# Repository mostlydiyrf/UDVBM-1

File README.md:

# UDVBM-1
Kicad (ver.6) design files, Arduino sketches, and user documents.

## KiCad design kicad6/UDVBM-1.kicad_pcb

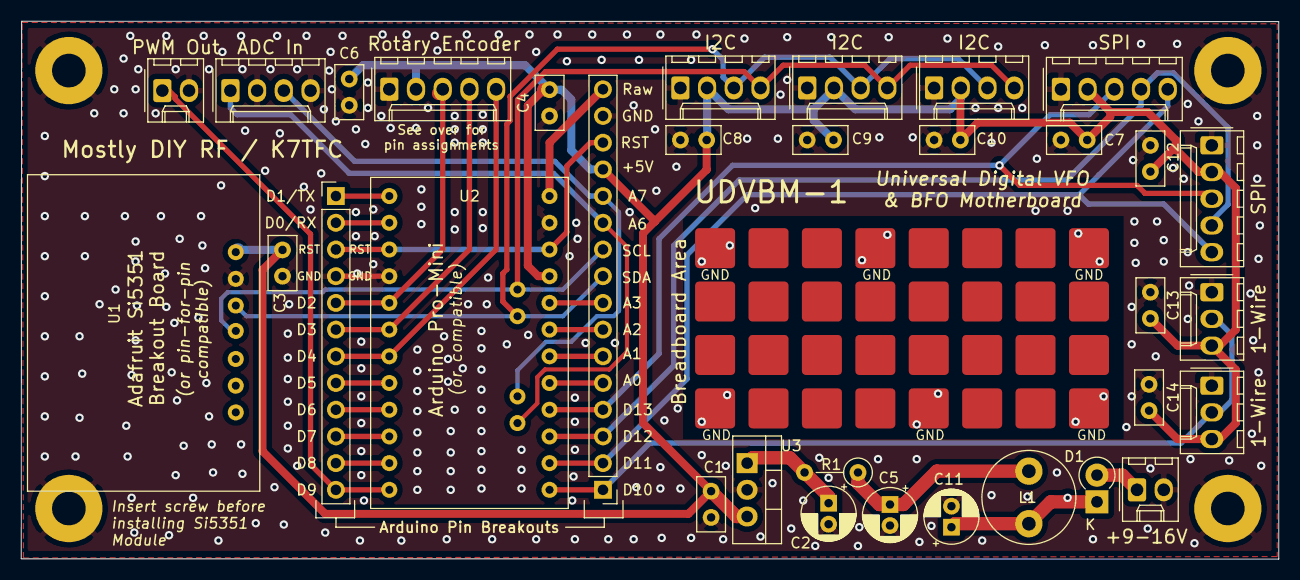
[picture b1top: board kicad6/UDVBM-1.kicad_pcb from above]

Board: 2 copper layers, 119.6 x 51.1 mm, 37 parts (0 on the bottom side), 30 nets.

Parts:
1-Wire: One-Wire Port 1; Molex_KK-254_AE-6410-03A_1x03_P2.54mm_Vertical
1-Wire#2: One-Wire Port 2; Molex_KK-254_AE-6410-03A_1x03_P2.54mm_Vertical
ADC In: ADC Inputs; Molex_KK-254_AE-6410-04A_1x04_P2.54mm_Vertical
C1, C3, C4, C6, C7, C8, C9, C10, C12, C13, C14: 0.10; C_Disc_D5.0mm_W2.5mm_P2.50mm
C2: 10uF; CP_Radial_D5.0mm_P2.00mm
C5, C11: 220uF; CP_Radial_D5.0mm_P2.00mm
D1: 1N4001; D_DO-41_SOD81_P2.54mm_Vertical_KathodeUp
H1, H2, H3, H4: Mounting_Hole_4-40; MountingHole_3.2mm_M3_Pad
I2C: I2C Port 1; Molex_KK-254_AE-6410-04A_1x04_P2.54mm_Vertical
I2C#2: I2C Port 3; Molex_KK-254_AE-6410-04A_1x04_P2.54mm_Vertical
I2C#3: I2C Port 2; Molex_KK-254_AE-6410-04A_1x04_P2.54mm_Vertical
J1: 12VDC; Molex_KK-254_AE-6410-02A_1x02_P2.54mm_Vertical
J2: Arduino Left Breakout; PinHeader_1x12_P2.54mm_Vertical
J3: Arduino Right Breakout; PinHeader_1x16_P2.54mm_Vertical
L1: 1.0mH; L_Radial_D8.7mm_P5.00mm_Fastron_07HCP
PWM Out: PWM Out; Molex_KK-254_AE-6410-02A_1x02_P2.54mm_Vertical
R1: 10; R_Axial_DIN0207_L6.3mm_D2.5mm_P5.08mm_Vertical
Rotary Encoder: Rotary Encoder; Molex_KK-254_AE-6410-05A_1x05_P2.54mm_Vertical
SPI: SPI Port 1; Molex_KK-254_AE-6410-05A_1x05_P2.54mm_Vertical
SPI#2: SPI Port 2; Molex_KK-254_AE-6410-05A_1x05_P2.54mm_Vertical
U1: Si5351A_Adafruit
U2: ArduinoPro_Mini; Arduino_Pro_Mini
U3: LM7805; TO-220-3_Vertical

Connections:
+5V: 1-Wire.3, 1-Wire#2.3, C1.1, C3.2, C4.2, C6.2, C7.2, C8.2, C9.2, C10.2, C12.2, C13.2, C14.2, I2C.2, I2C#2.2, I2C#3.2, J3.13, Rotary Encoder.2, SPI.2, SPI#2.2, U1.6, U2.22, U3.3
/1wire: 1-Wire.2, 1-Wire#2.2, J3.1, U2.10
/ADC1: ADC In.1, J3.11, U2.20
/ADC2: ADC In.3, J3.12, U2.21
/D0: J2.2, U2.0
/D1: J2.1, U2.1
/D2: J2.5, Rotary Encoder.3, U2.2
/D3: J2.6, Rotary Encoder.4, U2.3
/D4: J2.7, Rotary Encoder.5, U2.4
/D5: J2.8, U2.5
/D6: J2.9, U2.6
/D7: J2.10, U2.7
/D8: J2.11, U2.8
/D9: J2.12, PWM Out.1, U2.9
/D14: J3.5, U2.14
/D15: J3.6, U2.15
/D16: J3.7, U2.16
/D17: J3.8, U2.17
/MISO: J3.3, SPI.4, SPI#2.4, U2.12
/MOSI: J3.2, SPI.5, SPI#2.5, U2.11
/RST: J2.3, J3.14, U2.23, U2.27
/Raw: J3.16, U2.25
/SCK: J3.4, SPI.3, SPI#2.3, U2.13
/SCL: I2C.4, I2C#2.4, I2C#3.4, J3.10, U1.3, U2.19
/SDA: I2C.3, I2C#2.3, I2C#3.3, J3.9, U1.4, U2.18
GND: 1-Wire.1, 1-Wire#2.1, ADC In.2, ADC In.4, C1.2, C2.2, C3.1, C4.1, C5.2, C6.1, C7.1, C8.1, C9.1, C10.1, C11.2, C12.1, C13.1, C14.1, I2C.1, I2C#2.1, I2C#3.1, J1.2, J2.4, J3.15, PWM Out.2, Rotary Encoder.1, SPI.1, SPI#2.1, U1.5, U2.24, U2.26, U3.2
unnamed: C2.1, R1.2, U3.1
unnamed: C5.1, L1.1, R1.1
unnamed: C11.1, D1.1, L1.2
unnamed: D1.2, J1.1

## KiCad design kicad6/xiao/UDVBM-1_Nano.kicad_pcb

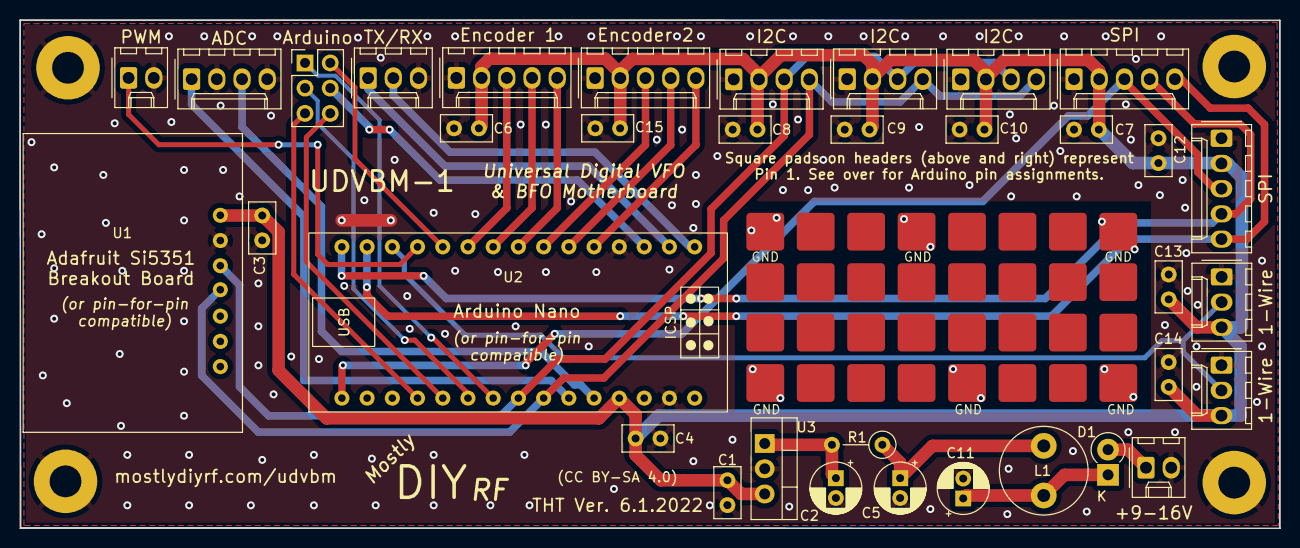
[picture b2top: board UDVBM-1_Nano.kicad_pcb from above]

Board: 2 copper layers, 126.9 x 51.2 mm, 39 parts (0 on the bottom side), 29 nets.

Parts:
1-Wire: One-Wire Port 1; Molex_KK-254_AE-6410-03A_1x03_P2.54mm_Vertical
1-Wire#2: One-Wire Port 2; Molex_KK-254_AE-6410-03A_1x03_P2.54mm_Vertical
ADC: ADC Inputs; Molex_KK-254_AE-6410-04A_1x04_P2.54mm_Vertical
Arduino: Arduino Pins; PinHeader_2x03_P2.54mm_Vertical
C1, C3, C4, C6, C7, C8, C9, C10, C12, C13, C14, C15: 0.10; C_Disc_D5.0mm_W2.5mm_P2.50mm
C2: 10uF; CP_Radial_D5.0mm_P2.00mm
C5, C11: 220uF; CP_Radial_D5.0mm_P2.00mm
D1: 1N4001; D_DO-41_SOD81_P2.54mm_Vertical_KathodeUp
Encoder 1: Rotary Encoder 1; Molex_KK-254_AE-6410-05A_1x05_P2.54mm_Vertical
Encoder 2: Rotary Encoder 2; Molex_KK-254_AE-6410-05A_1x05_P2.54mm_Vertical
H1, H2, H3, H4: Mounting_Hole_4-40; MountingHole_3.2mm_M3_Pad
I2C: I2C Port 1; Molex_KK-254_AE-6410-04A_1x04_P2.54mm_Vertical
I2C#2: I2C Port 3; Molex_KK-254_AE-6410-04A_1x04_P2.54mm_Vertical
I2C#3: I2C Port 2; Molex_KK-254_AE-6410-04A_1x04_P2.54mm_Vertical
J1: 12VDC; Molex_KK-254_AE-6410-02A_1x02_P2.54mm_Vertical
L1: 1.0mH; L_Radial_D8.7mm_P5.00mm_Fastron_07HCP
PWM: PWM Out; Molex_KK-254_AE-6410-02A_1x02_P2.54mm_Vertical
R1: 10; R_Axial_DIN0207_L6.3mm_D2.5mm_P5.08mm_Vertical
SPI: SPI Port 1; Molex_KK-254_AE-6410-05A_1x05_P2.54mm_Vertical
SPI#2: SPI Port 2; Molex_KK-254_AE-6410-05A_1x05_P2.54mm_Vertical
TX/RX: Serial RX/TX; Molex_KK-254_AE-6410-03A_1x03_P2.54mm_Vertical
U1: Si5351A_Adafruit
U2: Arduino_Nano
U3: LM7805; TO-220-3_Vertical

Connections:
+5V: 1-Wire.3, 1-Wire#2.3, C1.1, C3.2, C4.2, C6.2, C7.2, C8.2, C9.2, C10.2, C12.2, C13.2, C14.2, C15.2, Encoder 1.2 (+5V), Encoder 2.2 (+5V), I2C.2 (+5V), I2C#2.2 (+5V), I2C#3.2 (+5V), SPI.2, SPI#2.2, U1.6 (Vin), U2.5V (+5V), U3.3 (VO)
/1wire: 1-Wire.2, 1-Wire#2.2, U2.10 (D10)
/A(DT)1: Encoder 1.4 (A(DT)), U2.6 (D6)
/A(DT)2: Encoder 2.4 (A(DT)), U2.3 (D3)
/ADC1: ADC.1, U2.A6
/ADC2: ADC.3, U2.A7
/B(CLK)1: Encoder 1.5 (B(CLK)), U2.5 (D5)
/B(CLK)2: Encoder 2.5 (B(CLK)), U2.2 (D2)
/D8: Arduino.2, U2.8 (D8)
/D9: PWM.1, U2.9 (D9)
/D14: Arduino.5, U2.14 (D14/A0)
/D15: Arduino.6, U2.15 (D15/A1)
/D16: Arduino.3, U2.16 (D16/A2)
/D17: Arduino.1, U2.17 (D17/A3)
/MISO: SPI.4, SPI#2.4, U2.12 (D12)
/MOSI: SPI.5, SPI#2.5, U2.11 (D11)
/RST: Arduino.4, U2.RST1 (RST), U2.RST2 (RST)
/RX: TX/RX.2, U2.1 (D1/RX)
/SCK: SPI.3, SPI#2.3, U2.13 (D13)
/SCL: I2C.4 (SCL), I2C#2.4 (SCL), I2C#3.4 (SCL), U1.3 (SCL), U2.19 (A5/SCL)
/SDA: I2C.3 (SDA), I2C#2.3 (SDA), I2C#3.3 (SDA), U1.4 (SDA), U2.18 (A4/SDA)
/SW1: Encoder 1.3 (SW), U2.7 (D7)
/SW2: Encoder 2.3 (SW), U2.4 (D4)
/TX: TX/RX.1, U2.0 (D0/TX)
GND: 1-Wire.1, 1-Wire#2.1, ADC.2, ADC.4, C1.2, C2.2, C3.1, C4.1, C5.2, C6.1, C7.1, C8.1, C9.1, C10.1, C11.2, C12.1, C13.1, C14.1, C15.1, Encoder 1.1 (GND), Encoder 2.1 (GND), I2C.1 (GND), I2C#2.1 (GND), I2C#3.1 (GND), J1.2, PWM.2, SPI.1, SPI#2.1, TX/RX.3, U1.5 (GND), U2.GND1 (GND), U2.GND2 (GND), U3.2 (GND)
unnamed: C2.1, R1.2, U3.1 (VI)
unnamed: C5.1, L1.1, R1.1
unnamed: C11.1, D1.1 (K), L1.2
unnamed: D1.2 (A), J1.1

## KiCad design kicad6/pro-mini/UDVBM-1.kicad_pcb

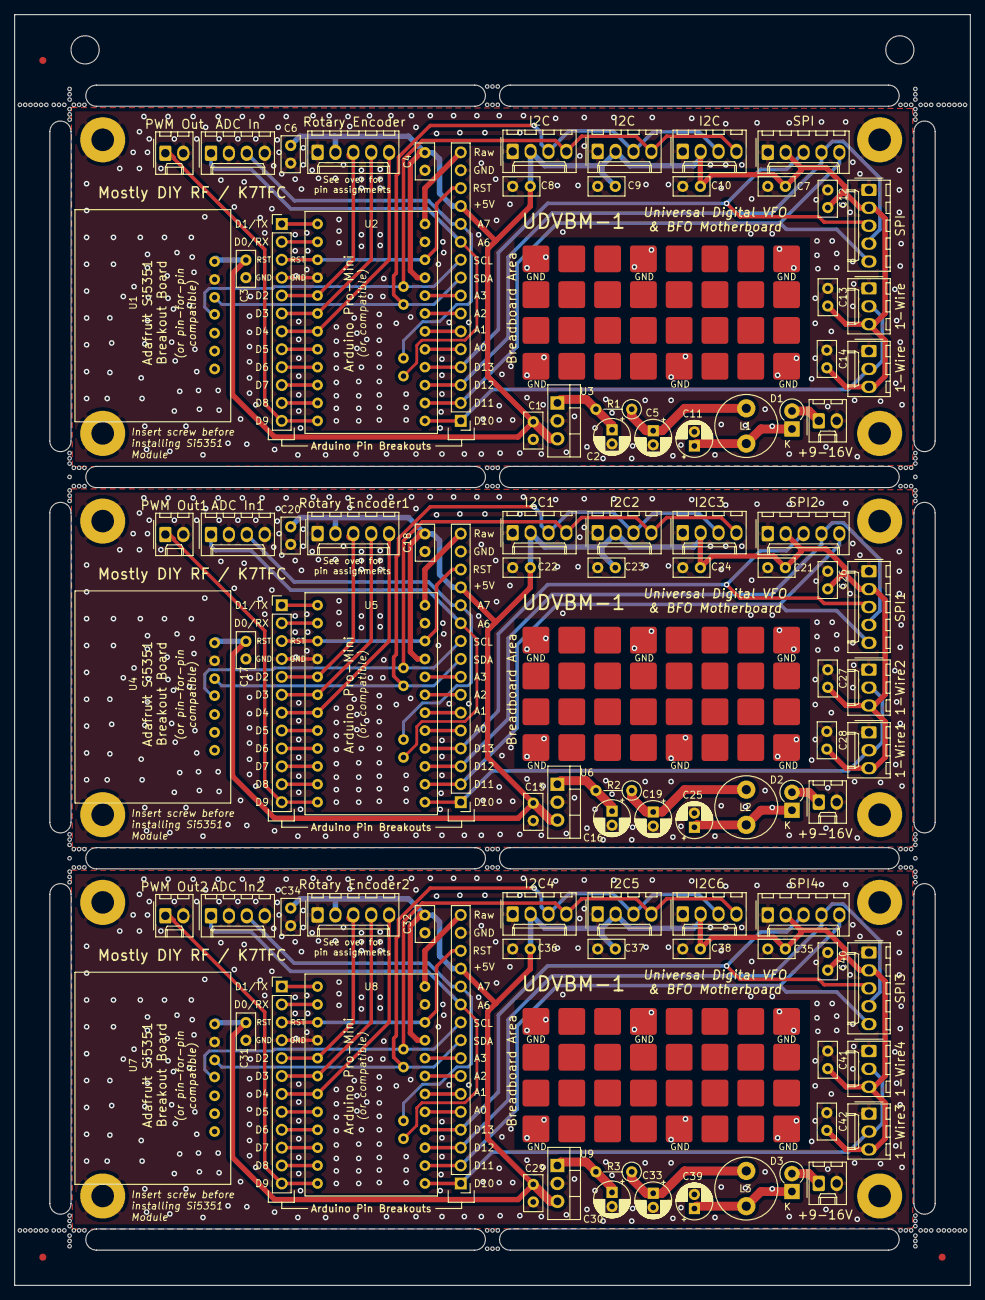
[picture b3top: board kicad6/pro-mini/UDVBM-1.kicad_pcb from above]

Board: 2 copper layers, 135.6 x 180.3 mm, 111 parts (0 on the bottom side), 33 nets.

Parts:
1-Wire, 1-Wire2, 1-Wire4: One-Wire Port 1; Molex_KK-254_AE-6410-03A_1x03_P2.54mm_Vertical
1-Wire1, 1-Wire3, 1-Wire#2: One-Wire Port 2; Molex_KK-254_AE-6410-03A_1x03_P2.54mm_Vertical
ADC In, ADC In1, ADC In2: ADC Inputs; Molex_KK-254_AE-6410-04A_1x04_P2.54mm_Vertical
C1, C3, C4, C6, C7, C8, C9, C10, C12, C13, C14, C15, C17, C18, C20, C21, C22, C23, C24, C26, C27, C28, C29, C31, C32, C34, C35, C36, C37, C38, C40, C41, C42: 0.10; C_Disc_D5.0mm_W2.5mm_P2.50mm
C2, C16, C30: 10uF; CP_Radial_D5.0mm_P2.00mm
C5, C11, C19, C25, C33, C39: 220uF; CP_Radial_D5.0mm_P2.00mm
D1, D2, D3: 1N4001; D_DO-41_SOD81_P2.54mm_Vertical_KathodeUp
H1, H2, H3, H4, H5, H6, H7, H8, H9, H10, H11, H12: Mounting_Hole_4-40; MountingHole_3.2mm_M3_Pad
I2C, I2C1, I2C4: I2C Port 1; Molex_KK-254_AE-6410-04A_1x04_P2.54mm_Vertical
I2C2, I2C5, I2C#3: I2C Port 2; Molex_KK-254_AE-6410-04A_1x04_P2.54mm_Vertical
I2C3, I2C6, I2C#2: I2C Port 3; Molex_KK-254_AE-6410-04A_1x04_P2.54mm_Vertical
J1, J4, J7: 12VDC; Molex_KK-254_AE-6410-02A_1x02_P2.54mm_Vertical
J2, J5, J8: Arduino Left Breakout; PinHeader_1x12_P2.54mm_Vertical
J3, J6, J9: Arduino Right Breakout; PinHeader_1x16_P2.54mm_Vertical
L1, L2, L3: 1.0mH; L_Radial_D8.7mm_P5.00mm_Fastron_07HCP
PWM Out, PWM Out1, PWM Out2: PWM Out; Molex_KK-254_AE-6410-02A_1x02_P2.54mm_Vertical
R1, R2, R3: 10; R_Axial_DIN0207_L6.3mm_D2.5mm_P5.08mm_Vertical
Rotary Encoder, Rotary Encoder1, Rotary Encoder2: Rotary Encoder; Molex_KK-254_AE-6410-05A_1x05_P2.54mm_Vertical
SPI, SPI2, SPI4: SPI Port 1; Molex_KK-254_AE-6410-05A_1x05_P2.54mm_Vertical
SPI1, SPI3: SPI Port 2; Molex_KK-254_AE-6410-05A_1x05_P2.54mm_Vertical
SPI#2: SPI Port 2; Molex_KK-254_AE-6410-05A_1x05_P2.54mm_Vertical
U1, U4, U7: Si5351A_Adafruit
U2, U5, U8: ArduinoPro_Mini; Arduino_Pro_Mini
U3, U6, U9: LM7805; TO-220-3_Vertical

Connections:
+5V: 1-Wire.3, 1-Wire1.3, 1-Wire2.3, 1-Wire3.3, 1-Wire4.3, 1-Wire#2.3, C1.1, C3.2, C4.2, C6.2, C7.2, C8.2, C9.2, C10.2, C12.2, C13.2, C14.2, C15.1, C17.2, C18.2, C20.2, C21.2, C22.2, C23.2, C24.2, C26.2, C27.2, C28.2, C29.1, C31.2, C32.2, C34.2, C35.2, C36.2, C37.2, C38.2, C40.2, C41.2, C42.2, I2C.2, I2C1.2, I2C2.2, I2C3.2, I2C4.2, I2C5.2, I2C6.2, I2C#2.2, I2C#3.2, J3.13, J6.13, J9.13, Rotary Encoder.2, Rotary Encoder1.2, Rotary Encoder2.2, SPI.2, SPI1.2, SPI2.2, SPI3.2, SPI4.2, SPI#2.2, U1.6, U2.22, U3.3, U4.6, U5.22, U6.3, U7.6, U8.22, U9.3
/1wire: 1-Wire.2, 1-Wire1.2, 1-Wire2.2, 1-Wire3.2, 1-Wire4.2, 1-Wire#2.2, J3.1, J6.1, J9.1, U2.10, U5.10, U8.10
/ADC1: ADC In.1, ADC In1.1, ADC In2.1, J3.11, J6.11, J9.11, U2.20, U5.20, U8.20
/ADC2: ADC In.3, ADC In1.3, ADC In2.3, J3.12, J6.12, J9.12, U2.21, U5.21, U8.21
/D0: J2.2, J5.2, J8.2, U2.0, U5.0, U8.0
/D1: J2.1, J5.1, J8.1, U2.1, U5.1, U8.1
/D2: J2.5, J5.5, J8.5, Rotary Encoder.3, Rotary Encoder1.3, Rotary Encoder2.3, U2.2, U5.2, U8.2
/D3: J2.6, J5.6, J8.6, Rotary Encoder.4, Rotary Encoder1.4, Rotary Encoder2.4, U2.3, U5.3, U8.3
/D4: J2.7, J5.7, J8.7, Rotary Encoder.5, Rotary Encoder1.5, Rotary Encoder2.5, U2.4, U5.4, U8.4
/D5: J2.8, J5.8, J8.8, U2.5, U5.5, U8.5
/D6: J2.9, J5.9, J8.9, U2.6, U5.6, U8.6
/D7: J2.10, J5.10, J8.10, U2.7, U5.7, U8.7
/D8: J2.11, J5.11, J8.11, U2.8, U5.8, U8.8
/D9: J2.12, J5.12, J8.12, PWM Out.1, PWM Out1.1, PWM Out2.1, U2.9, U5.9, U8.9
/D14: J3.5, J6.5, J9.5, U2.14, U5.14, U8.14
/D15: J3.6, J6.6, J9.6, U2.15, U5.15, U8.15
/D16: J3.7, J6.7, J9.7, U2.16, U5.16, U8.16
/D17: J3.8, J6.8, J9.8, U2.17, U5.17, U8.17
/MISO: J3.3, J6.3, J9.3, SPI.4, SPI1.4, SPI2.4, SPI3.4, SPI4.4, SPI#2.4, U2.12, U5.12, U8.12
/MOSI: J3.2, J6.2, J9.2, SPI.5, SPI1.5, SPI2.5, SPI3.5, SPI4.5, SPI#2.5, U2.11, U5.11, U8.11
/RST: J2.3, J3.14, J5.3, J6.14, J8.3, J9.14, U2.23, U2.27, U5.23, U5.27, U8.23, U8.27
/Raw: J3.16, J6.16, J9.16, U2.25, U5.25, U8.25
/SCK: J3.4, J6.4, J9.4, SPI.3, SPI1.3, SPI2.3, SPI3.3, SPI4.3, SPI#2.3, U2.13, U5.13, U8.13
/SCL: I2C.4, I2C1.4, I2C2.4, I2C3.4, I2C4.4, I2C5.4, I2C6.4, I2C#2.4, I2C#3.4, J3.10, J6.10, J9.10, U1.3, U2.19, U4.3, U5.19, U7.3, U8.19
/SDA: I2C.3, I2C1.3, I2C2.3, I2C3.3, I2C4.3, I2C5.3, I2C6.3, I2C#2.3, I2C#3.3, J3.9, J6.9, J9.9, U1.4, U2.18, U4.4, U5.18, U7.4, U8.18
GND: 1-Wire.1, 1-Wire1.1, 1-Wire2.1, 1-Wire3.1, 1-Wire4.1, 1-Wire#2.1, ADC In.2, ADC In.4, ADC In1.2, ADC In1.4, ADC In2.2, ADC In2.4, C1.2, C2.2, C3.1, C4.1, C5.2, C6.1, C7.1, C8.1, C9.1, C10.1, C11.2, C12.1, C13.1, C14.1, C15.2, C16.2, C17.1, C18.1, C19.2, C20.1, C21.1, C22.1, C23.1, C24.1, C25.2, C26.1, C27.1, C28.1, C29.2, C30.2, C31.1, C32.1, C33.2, C34.1, C35.1, C36.1, C37.1, C38.1, C39.2, C40.1, C41.1, C42.1, I2C.1, I2C1.1, I2C2.1, I2C3.1, I2C4.1, I2C5.1, I2C6.1, I2C#2.1, I2C#3.1, J1.2, J2.4, J3.15, J4.2, J5.4, J6.15, J7.2, J8.4, J9.15, PWM Out.2, PWM Out1.2, PWM Out2.2, Rotary Encoder.1, Rotary Encoder1.1, Rotary Encoder2.1, SPI.1, SPI1.1, SPI2.1, SPI3.1, SPI4.1, SPI#2.1, U1.5, U2.24, U2.26, U3.2, U4.5, U5.24, U5.26, U6.2, U7.5, U8.24, U8.26, U9.2
unnamed: C2.1, C16.1, C30.1, R1.2, R2.2, R3.2, U3.1, U6.1, U9.1
unnamed: C5.1, C19.1, C33.1, L1.1, L2.1, L3.1, R1.1, R2.1, R3.1
unnamed: C11.1, C25.1, C39.1, D1.1, D2.1, D3.1, L1.2, L2.2, L3.2
unnamed: D1.2, D2.2, D3.2, J1.1, J4.1, J7.1
unnamed: U1.0, U4.0, U7.0
unnamed: U1.1, U4.1, U7.1
unnamed: U1.2, U4.2, U7.2

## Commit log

2022-04-06 Create .gitkeep
    remove after adding other files for /doc folder.
2022-08-17 Delete UDVBM-1_schematic.pdf
    Replaced with combined PDF
2022-08-17 Add files via upload
    Replaced single with combined PDF
2025-05-26 Add files via upload
    Updated version with new material on one-wire analog bus implementation in Arduino code

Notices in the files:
kicad6/UDVBM-1.kicad_pcb:
(CC BY-SA 4.0)
